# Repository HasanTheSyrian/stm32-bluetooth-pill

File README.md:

# STM32 Bluetooth Development Board
*hasn't been assembled and tested yet, there is a non-public version that uses a chip antenna

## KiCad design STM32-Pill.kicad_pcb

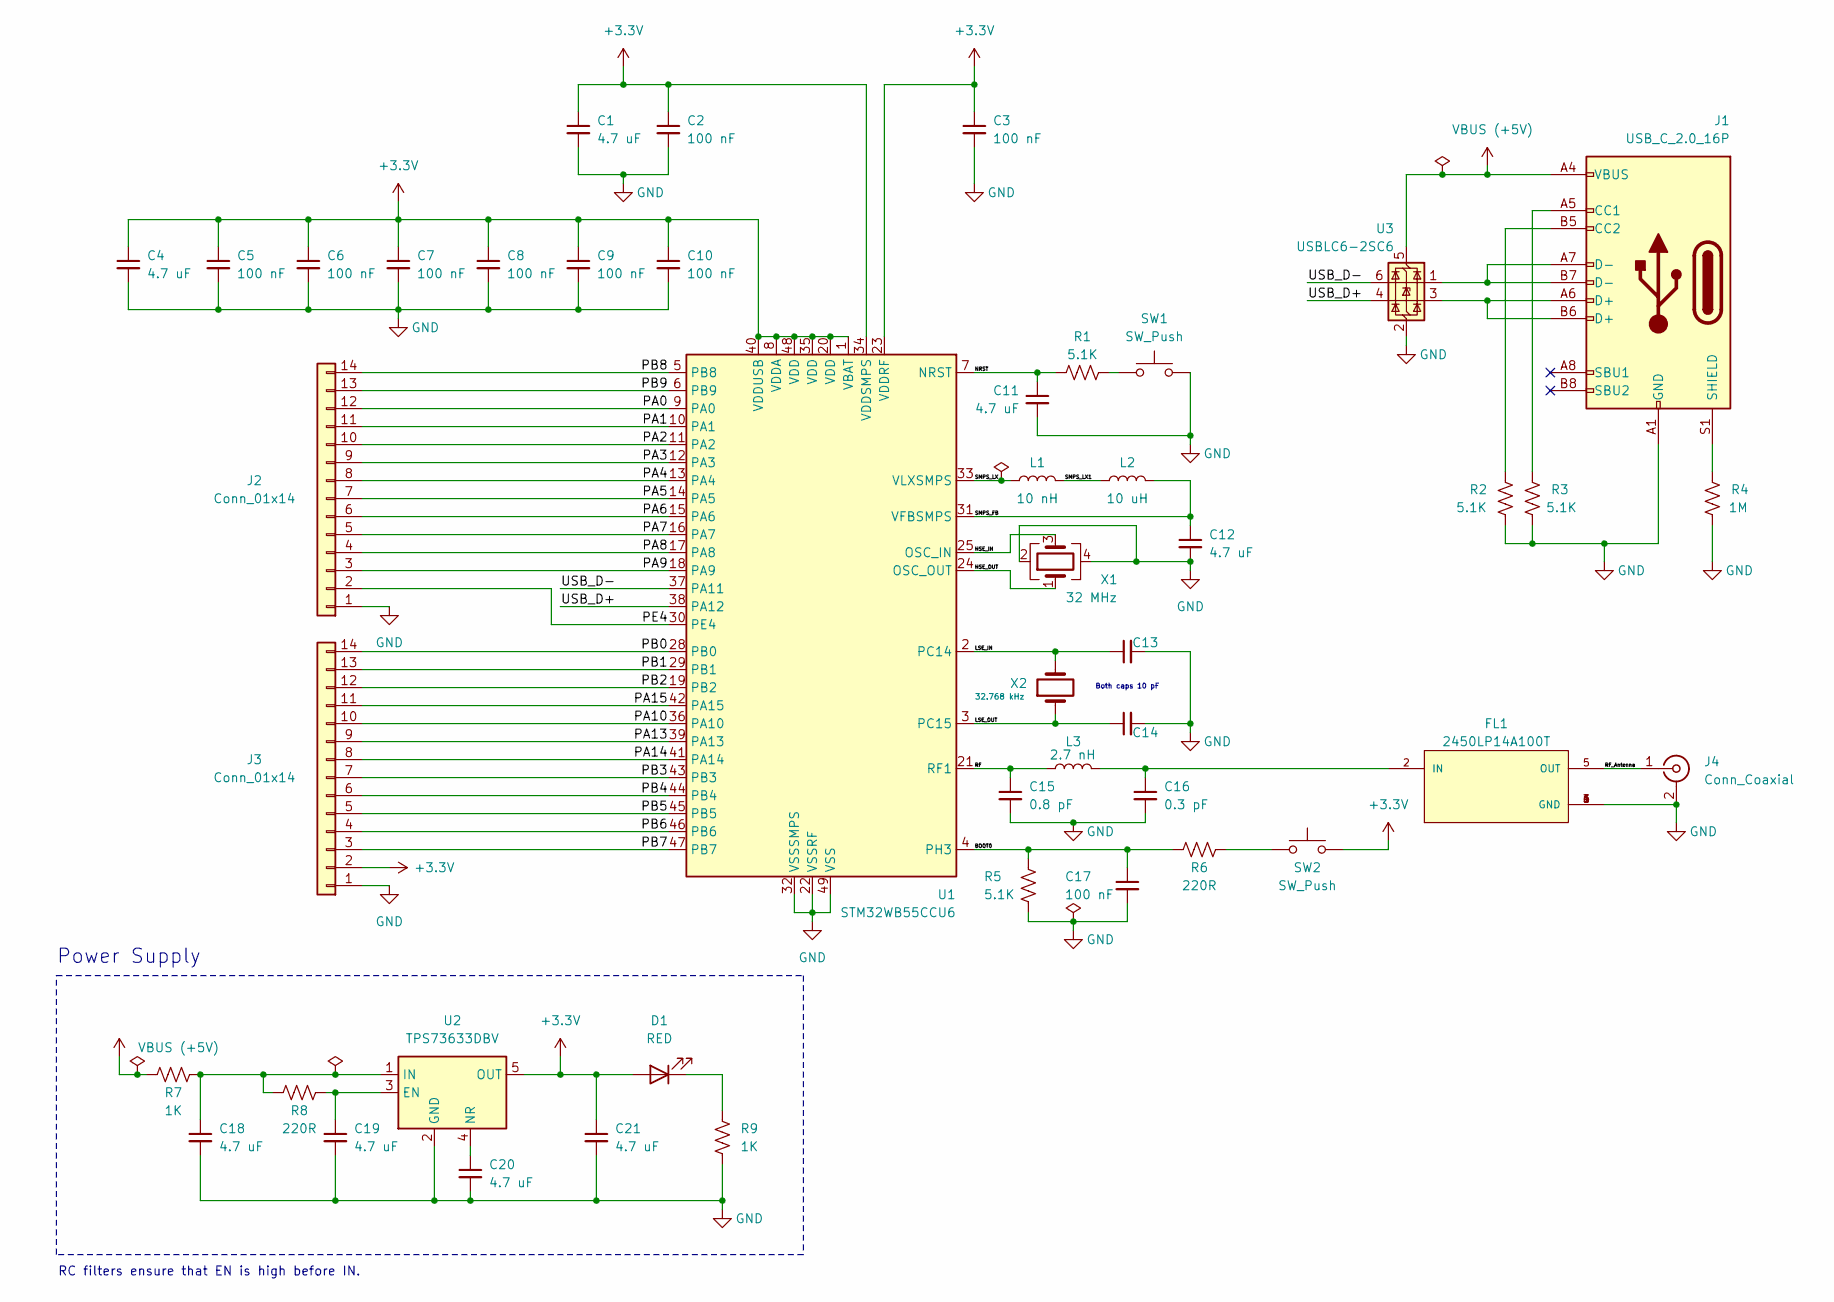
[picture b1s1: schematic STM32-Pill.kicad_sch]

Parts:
C1, C4, C11, C12, C18, C19, C20, C21: 4.7 uF; C_0805_2012Metric
C2, C3, C5, C6, C7, C8, C9, C10, C17: 100 nF; C_0805_2012Metric
C13, C14: 10 pF; C_0805_2012Metric
C15: 0.8 pF; C_0402_1005Metric
C16: 0.3 pF; C_0201_0603Metric_Pad0.64x0.40mm_HandSolder
D1: RED; D_1206_3216Metric_Pad1.42x1.75mm_HandSolder
FL1: 2450LP14A100T; ICCAF50P160X80X70-6N; PARTREV 06/23/03
J1: USB_C_2.0_16P; USB_C_Receptacle_GCT_USB4105-xx-A_16P_TopMnt_Horizontal
J2, J3: Conn_01x14; PinHeader_1x14_P2.54mm_Vertical
J4: Conn_Coaxial; U.FL_Hirose_U.FL-R-SMT-1_Vertical
L1: 10 nH; L_0805_2012Metric
L2: 10 uH; L_0805_2012Metric
L3: 2.7 nH; L_0402_1005Metric
R1, R2, R3, R5: 5.1K; R_0805_2012Metric
R4: 1M; R_0805_2012Metric
R6, R8: 220R; R_0805_2012Metric
R7, R9: 1K; R_0805_2012Metric
SW1, SW2: SW_Push; SW_SPST_CK_RS282G05A3
U1: STM32WB55CCU6; STM32WB-QFN50P700X700X60-49N
U2: TPS73633DBV; SOT-23-5_HandSoldering
U3: USBLC6-2SC6; SOT95P280X145-6N
X1: 32 MHz; Crystal_SMD_SeikoEpson_FA128-4Pin_2.0x1.6mm
X2: 32.768 kHz; Crystal_SMD_3215-2Pin_3.2x1.5mm

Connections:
+3.3V: C1.1, C2.1, C3.1, C4.1, C5.1, C6.1, C7.1, C8.1, C9.1, C10.1, C21.1, D1.2 (A), J3.2, SW2.2, U1.1 (VBAT), U1.8 (VDDA), U1.20 (VDD), U1.23 (VDDRF), U1.34 (VDDSMPS), U1.35 (VDD), U1.40 (VDDUSB), U1.48 (VDD), U2.5 (OUT); also elsewhere on the board
/BOOT0: C17.1, R5.2, R6.2, U1.4 (PH3)
/HSE_IN: U1.25 (OSC_IN), X1.3
/HSE_OUT: U1.24 (OSC_OUT), X1.1
/LSE_IN: C13.1, U1.2 (PC14), X2.2
/LSE_OUT: C14.1, U1.3 (PC15), X2.1
/NRST: C11.1, R1.2, U1.7 (NRST)
/PA0: J2.12, U1.9 (PA0)
/PA1: J2.11, U1.10 (PA1)
/PA2: J2.10, U1.11 (PA2)
/PA3: J2.9, U1.12 (PA3)
/PA4: J2.8, U1.13 (PA4)
/PA5: J2.7, U1.14 (PA5)
/PA6: J2.6, U1.15 (PA6)
/PA7: J2.5, U1.16 (PA7)
/PA8: J2.4, U1.17 (PA8)
/PA9: J2.3, U1.18 (PA9)
/PA10: J3.10, U1.36 (PA10)
/PA13: J3.9, U1.39 (PA13)
/PA14: J3.8, U1.41 (PA14)
/PA15: J3.11, U1.42 (PA15)
/PB0: J3.14, U1.28 (PB0)
/PB1: J3.13, U1.29 (PB1)
/PB2: J3.12, U1.19 (PB2)
/PB3: J3.7, U1.43 (PB3)
/PB4: J3.6, U1.44 (PB4)
/PB5: J3.5, U1.45 (PB5)
/PB6: J3.4, U1.46 (PB6)
/PB7: J3.3, U1.47 (PB7)
/PB8: J2.14, U1.5 (PB8)
/PB9: J2.13, U1.6 (PB9)
/PE4: J2.2, U1.30 (PE4)
/RF: C15.1, L3.1, U1.21 (RF1)
/RF_Antenna: FL1.5 (OUT), J4.1 (In)
/SMPS_FB: C12.1, L2.2, U1.31 (VFBSMPS)
/SMPS_LX: L1.1, U1.33 (VLXSMPS)
/SMPS_LX1: L1.2, L2.1
/USB_D+: U1.38 (PA12), U3.4 (I/O2)
/USB_D-: U1.37 (PA11), U3.6 (I/O1)
GND: C1.2, C2.2, C3.2, C4.2, C5.2, C6.2, C7.2, C8.2, C9.2, C10.2, C11.2, C12.2, C13.2, C14.2, C15.2, C16.2, C17.2, C18.2, C19.2, C20.2, C21.2, FL1.1 (GND), FL1.3 (GND), FL1.4 (GND), FL1.6 (GND), J1.A1 (GND), J1.A12 (GND), J1.B1 (GND), J1.B12 (GND), J2.1, J3.1, J4.2 (Ext), R2.2, R3.2, R4.2, R5.1, R9.2, SW1.2, U1.22 (VSSRF), U1.32 (VSSSMPS), U1.49 (VSS), U2.2 (GND), U3.2 (GND), X1.2, X1.4
unnamed: D1.1 (K), R9.1
unnamed: C16.1, FL1.2 (IN), L3.2
unnamed: J1.A5 (CC1), R3.1
unnamed: J1.B5 (CC2), R2.1
unnamed: J1.A6 (D+), J1.B6 (D+), U3.3 (I/O2)
unnamed: J1.A7 (D-), J1.B7 (D-), U3.1 (I/O1)
unnamed: J1.S1 (SHIELD), R4.1
unnamed: R1.1, SW1.1
unnamed 48: R6.1, SW2.1; also elsewhere on the board
unnamed: C19.1, R8.1, U2.3 (EN)
unnamed: C18.1, R7.1, R8.2, U2.1 (IN)
unnamed: C20.1, U2.4 (NR)
VBUS (+5V): J1.A4 (VBUS), J1.A9 (VBUS), J1.B4 (VBUS), J1.B9 (VBUS), R7.2, U3.5 (VBUS)

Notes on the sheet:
Both caps 10 pF
RC filters ensure that EN is high before IN.
Power Supply

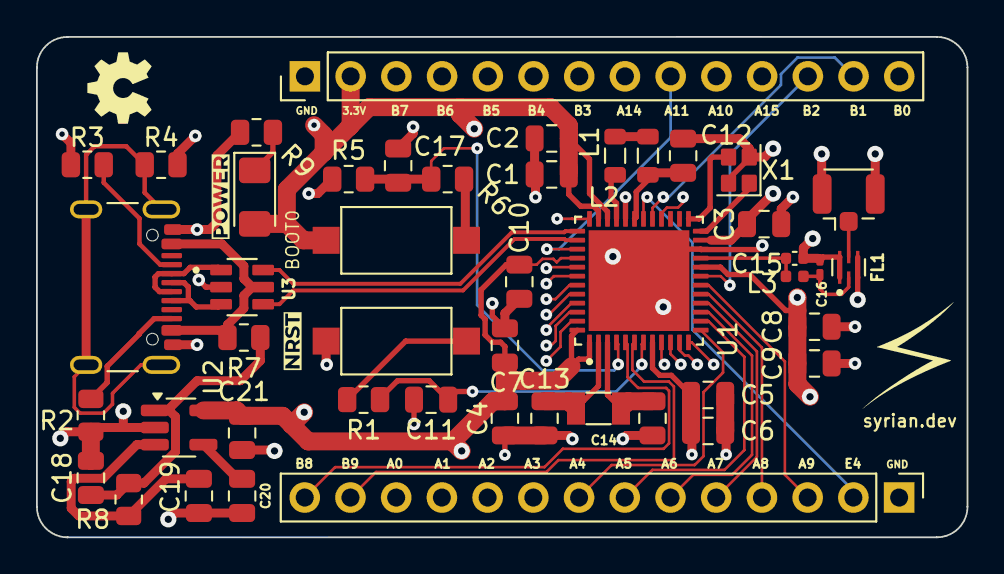
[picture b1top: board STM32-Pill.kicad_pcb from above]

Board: 6 copper layers, 51.7 x 27.8 mm, 46 parts (0 on the bottom side), 53 nets.

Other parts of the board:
BOOT0: SW_Push; SW_SPST_CK_RS282G05A3

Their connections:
+3.3V: BOOT0.2; also elsewhere on the board
unnamed 48: BOOT0.1; also elsewhere on the board

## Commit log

2025-02-23 first
